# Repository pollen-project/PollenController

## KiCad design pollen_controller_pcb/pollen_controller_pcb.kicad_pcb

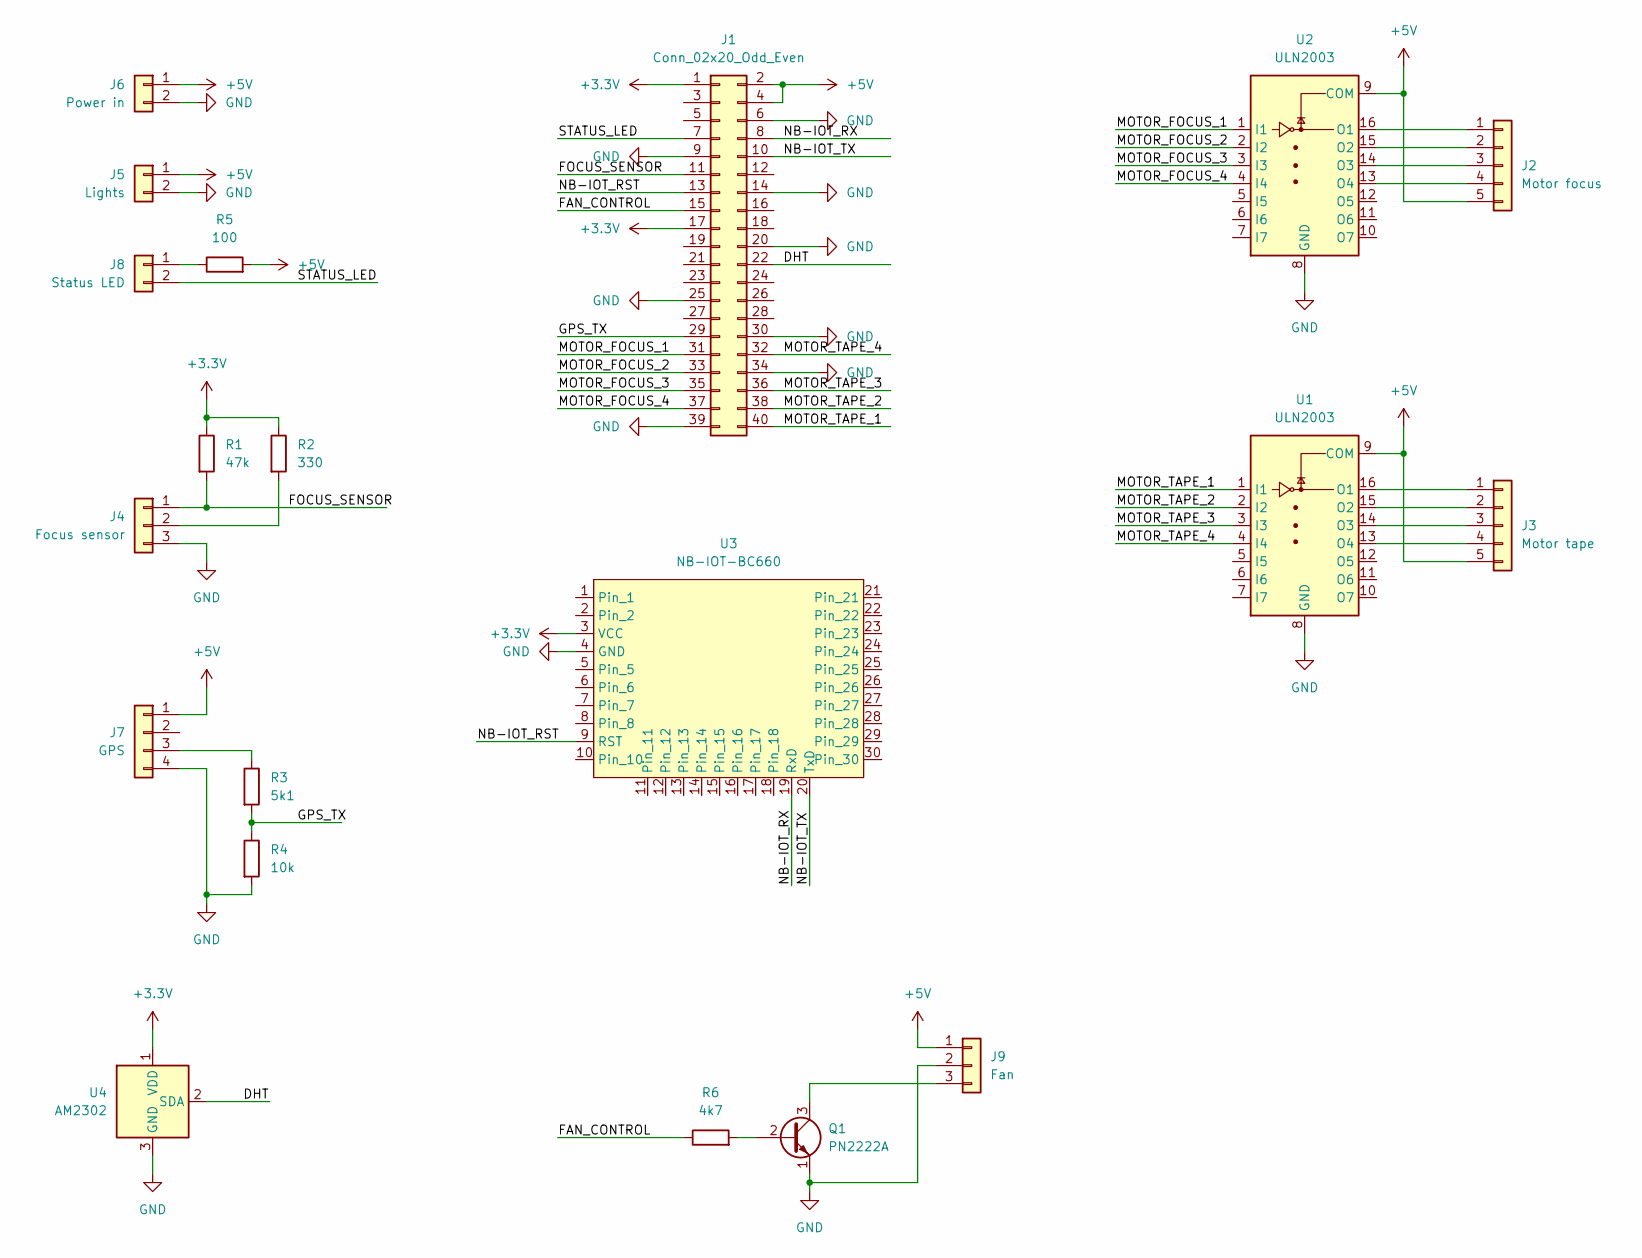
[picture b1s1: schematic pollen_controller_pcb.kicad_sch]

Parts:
J1: Conn_02x20_Odd_Even; PinSocket_2x20_P2.54mm_Vertical
J2: Motor focus; PinHeader_1x05_P2.54mm_Vertical
J3: Motor tape; PinHeader_1x05_P2.54mm_Vertical
J4: Focus sensor; PinSocket_1x03_P2.54mm_Vertical
J5: Lights; PinSocket_1x02_P2.54mm_Vertical
J6: Power in; PinSocket_1x02_P2.54mm_Vertical
J7: GPS; PinHeader_1x04_P2.54mm_Vertical
J8: Status LED; PinSocket_1x02_P2.54mm_Vertical
J9: Fan; PinSocket_1x03_P2.54mm_Vertical
Q1: PN2222A; TO-92L_HandSolder
R1: 47k; R_Axial_DIN0207_L6.3mm_D2.5mm_P10.16mm_Horizontal
R2: 330; R_Axial_DIN0207_L6.3mm_D2.5mm_P10.16mm_Horizontal
R3: 5k1; R_Axial_DIN0207_L6.3mm_D2.5mm_P10.16mm_Horizontal
R4: 10k; R_Axial_DIN0207_L6.3mm_D2.5mm_P10.16mm_Horizontal
R5: 100; R_Axial_DIN0207_L6.3mm_D2.5mm_P10.16mm_Horizontal
R6: 4k7; R_Axial_DIN0207_L6.3mm_D2.5mm_P10.16mm_Horizontal
U1, U2: ULN2003; DIP-16_W7.62mm_Socket
U3: NB-IOT-BC660
U4: AM2302; ASAIR_AM2302_P2.54mm_Vertical

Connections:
+3.3V: J1.1, J1.17, R1.1, R2.1, U3.3 (VCC), U4.1 (VDD)
+5V: J1.2, J1.4, J2.5, J3.5, J5.1, J6.1, J7.1, J9.1, R5.2, U1.9 (COM), U2.9 (COM)
/DHT: J1.22, U4.2 (SDA)
/FAN_CONTROL: J1.15, R6.1
/FOCUS_SENSOR: J1.11, J4.1, R1.2
/GPS_TX: J1.29, R3.2, R4.1
/MOTOR_FOCUS_1: J1.31, U2.1 (I1)
/MOTOR_FOCUS_2: J1.33, U2.2 (I2)
/MOTOR_FOCUS_3: J1.35, U2.3 (I3)
/MOTOR_FOCUS_4: J1.37, U2.4 (I4)
/MOTOR_TAPE_1: J1.40, U1.1 (I1)
/MOTOR_TAPE_2: J1.38, U1.2 (I2)
/MOTOR_TAPE_3: J1.36, U1.3 (I3)
/MOTOR_TAPE_4: J1.32, U1.4 (I4)
/NB-IOT_RST: J1.13, U3.9 (RST)
/NB-IOT_RX: J1.8, U3.19 (RxD)
/NB-IOT_TX: J1.10, U3.20 (TxD)
/STATUS_LED: J1.7, J8.2
GND: J1.6, J1.9, J1.14, J1.20, J1.25, J1.30, J1.34, J1.39, J4.3, J5.2, J6.2, J7.4, J9.2, Q1.1 (E), R4.2, U1.8 (GND), U2.8 (GND), U3.4 (GND), U4.3 (GND), U4.4 (GND)
unnamed: J2.1, U2.16 (O1)
unnamed: J2.2, U2.15 (O2)
unnamed: J2.3, U2.14 (O3)
unnamed: J2.4, U2.13 (O4)
unnamed: J3.1, U1.16 (O1)
unnamed: J3.2, U1.15 (O2)
unnamed: J3.3, U1.14 (O3)
unnamed: J3.4, U1.13 (O4)
unnamed: J4.2, R2.2
unnamed: J7.3, R3.1
unnamed: J8.1, R5.1
unnamed: J9.3, Q1.3 (C)
unnamed: Q1.2 (B), R6.2

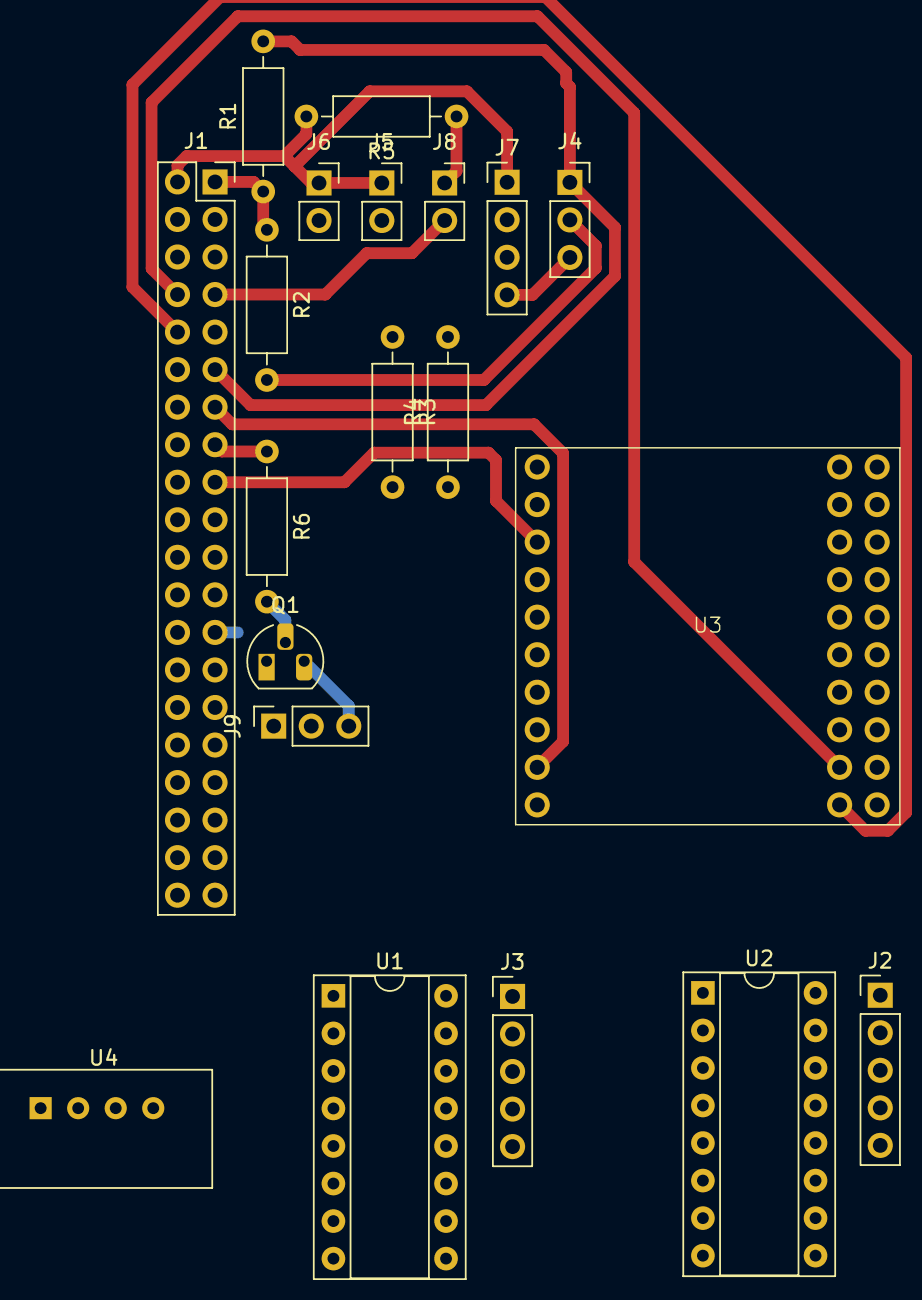
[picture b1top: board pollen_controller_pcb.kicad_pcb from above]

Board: 2 copper layers, 20 parts (0 on the bottom side), 32 nets.

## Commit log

2025-02-06 Add stepper motor test codes
2025-02-10 Add camera stream server
2025-02-10 autofocus and streaming working
2025-02-17 update greyscale
2025-02-17 Fix motor direction
2025-02-17 Startup focusing
2025-02-18 Reset position on startup to limit switch
2025-02-25 Change motor gpios
2025-02-28 push
2025-03-11 New focusing algorithm in stream_server
2025-03-11 Add image denoise
2025-03-11 New motor and focus control
2025-03-11 Add gitignore
2025-03-11 Refractoring init
2025-03-11 First Pollen Stream Controll panel implementation (webpage.html)
2025-03-11 Implemented stream zoom in / zoom out / reset size
2025-03-11 Fixed zoom for stream
2025-03-11 Fixed zoom again
2025-03-11 fixed zoom again / redesigned the page / more modern and simple look
2025-03-11 fixed small margin issue
2025-03-13 Added horizontal mode and vertical mode for the window / Fixed window cropping issue
2025-03-13 First implementation of making the buttons work
2025-03-13 Fixed problem with zoom in stream (grabs picture when trying to move around the picture)
2025-03-13 Enable optional image denoising
2025-03-13 Move command handling to separate file
2025-03-13 spike through http
2025-03-13 Dashboard works
2025-03-14 Added Denoise and Color/Greyscale functionality and buttons for the website
2025-03-14 Fixed cropping issue in vertical and horizontal mode on website
2025-03-14 Fixed problem with cropping again
2025-03-14 Added status bar on website
2025-03-14 Fixed host issue
2025-03-14 Minor code organisation
2025-03-14 added logo to website
2025-03-17 Fix denoise for stream
2025-03-17 Color denoising
2025-03-17 color denoising fix
2025-03-20 Change motor controller
2025-03-21 Take differet pics
2025-03-21 Try to fix image flags
2025-03-21 Fix denoise modes
2025-03-25 Refactor motor.py
2025-03-27 Add automation
2025-03-28 sorting interface
2025-03-28 Fixed endless focus
2025-03-28 Added DHT22 / NB-iot / GPS files for functionality
2025-03-31 Add PCB
2025-03-31 Fix typo
2025-04-01 Focus HUGE improvement - vary nice yes yes
2025-04-03 TEST_EXPOSURE_TIME_SEC changed from 60 to 120
2025-04-07 Implemented fan and fan controlls
2025-04-07 Added fan commands
2025-04-07 Upload image via post
2025-04-08 Upload to api
2025-04-08 Added fan functions / added fan commands to commands.py / added fan buttons on webpage
2025-04-08 Uploading to botond server
2025-04-08 Added fan automation to take_picture and take_picture_all
2025-04-08 Revert "Added fan automation to take_picture and take_picture_all"
    This reverts commit 9a3be5907f27e0e8f462276ffcb0de58b1efb162.
2025-04-08 Fan_on and fan_off corrected / made fan automation
2025-04-08 Set TEST_EXPOSURE_TIME_SEC to 300 it was to low before
2025-04-10 PCB changes
2025-04-10 Add some old test scripts
2025-04-14 Add schematic pdf
2025-04-15 Change gpios
2025-04-15 added DHT22 functionality
2025-04-15 Tried to implement DHT22
2025-04-15 Update GPS reading
2025-04-22 Change tape steps
2025-04-22 Send temperature and humidity
2025-04-22 Send GPS data
2025-04-24 Send detected pollen count to API
2025-04-24 Fix GPS readline error
2025-04-24 Run the model on camera image WIP
2025-04-25 Run the model on camera image
2025-04-25 Fix uploading data type
2025-04-28 Always take grayscale images
2025-05-02 Add backend/API
2025-05-02 Add pollen detections API endpoint
2025-05-21 Add 3D model STL files
2025-06-17 Add "from" parameter to the detections API endpoint
